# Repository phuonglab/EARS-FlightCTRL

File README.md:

# EARS-ROC
Rocket Onboard Computer designed for amateur rocketry. Light, modular and cheap.

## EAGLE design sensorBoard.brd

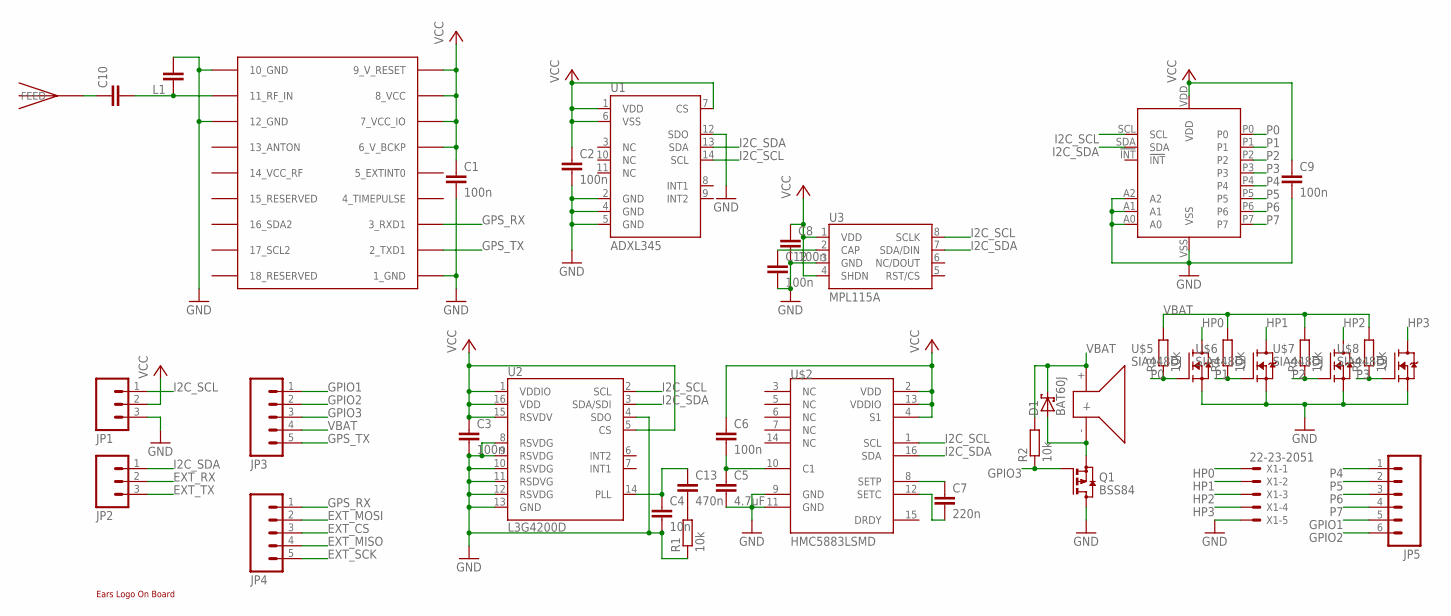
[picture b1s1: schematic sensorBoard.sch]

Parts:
C1, C2, C3, C6, C8, C9, C12: 100n; C0402
C4: 10n; C0402
C5: 4.7uF; C0402
C7: 220n; C0402
C10: C-EUC0603; C0603
C13: 470n; C0402
D1: BAT60J; SOD323_ST
JP1, JP2: M03PTH; 1X03
JP3, JP4: M05PTH; 1X05
JP5: M06SIP; 1X06
L1: C-EUC0603; C0603
Q1: BSS84; SOT23
R1, R2, R3, R4, R5, R6: 10k; R0402
U1: ADXL345; LGA14
U2: L3G4200D; LGA16-4X4
U3: MPL115A; LGA8
U$1: UBLOX_MAX
U$2: HMC5883LSMD; 16LPCC
U$3: KSSG23J12
U$4: PCAL9554B
U$5, U$6, U$7, U$8: SIA448DJ
U$9: JTI_ANTENNA-1575AT43A40
U$10: EARS-LOGO
X1: 22-23-2051

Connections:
EXT_CS: JP4.3
EXT_MISO: JP4.4
EXT_MOSI: JP4.2
EXT_RX: JP2.2
EXT_SCK: JP4.5
EXT_TX: JP2.3
GND: C1.2, C2.2, C3.2, C4.2, C5.2, C8.2, C9.2, C12.2, JP1.3, L1.2, Q1.3 (D), R1.1, U1.2 (GND), U1.4 (GND), U1.5 (GND), U1.12 (SDO), U2.4 (SDO), U2.8 (RSVDG), U2.9 (RSVDG), U2.10 (RSVDG), U2.11 (RSDVG), U2.12 (RSVDG), U2.13 (GND), U3.3 (GND), U$1.1_GND, U$1.10_GND, U$1.12_GND, U$2.9 (GND), U$2.11 (GND), U$4.A0, U$4.A1, U$4.A2, U$4.VSS, U$5.S0 (S), U$5.S4 (S), U$6.S0 (S), U$6.S4 (S), U$7.S0 (S), U$7.S4 (S), U$8.S0 (S), U$8.S4 (S), X1.5
GPIO1: JP3.1, JP5.5
GPIO2: JP3.2, JP5.6
GPIO3: JP3.3, Q1.1 (G), R2.1
GPS_RX: JP4.1, U$1.3_RXD1
GPS_TX: JP3.5, U$1.2_TXD1
HP0: U$5.D0 (D), U$5.D1 (D), U$5.D2 (D), U$5.D5 (D), U$5.D6 (D), X1.1
HP1: U$6.D0 (D), U$6.D1 (D), U$6.D2 (D), U$6.D5 (D), U$6.D6 (D), X1.2
HP2: U$7.D0 (D), U$7.D1 (D), U$7.D2 (D), U$7.D5 (D), U$7.D6 (D), X1.3
HP3: U$8.D0 (D), U$8.D1 (D), U$8.D2 (D), U$8.D5 (D), U$8.D6 (D), X1.4
I2C_SCL: JP1.1, U1.14 (SCL), U2.2 (SCL), U3.8 (SCLK), U$2.1 (SCL), U$4.SCL
I2C_SDA: JP2.1, U1.13 (SDA), U2.3 (SDA/SDI), U3.7 (SDA/DIN), U$2.16 (SDA), U$4.SDA
unnamed: C4.1, C13.1, U2.14 (PLL)
unnamed: C5.1, C6.2, U$2.10 (C1)
unnamed: C7.2, U$2.12 (SETC)
unnamed: C7.1, U$2.8 (SETP)
unnamed: D1.A, Q1.2 (S), U$3.-
unnamed: C10.1, U$9.FEED
unnamed: C10.2, L1.1, U$1.11_RF_IN
unnamed: C12.1, U3.2 (CAP)
unnamed: C13.2, R1.2
P0: R3.1, U$4.P0, U$5.G3 (G)
P1: R4.1, U$4.P1, U$6.G3 (G)
P2: R5.1, U$4.P2, U$7.G3 (G)
P3: R6.1, U$4.P3, U$8.G3 (G)
P4: JP5.1, U$4.P4
P5: JP5.2, U$4.P5
P6: JP5.3, U$4.P6
P7: JP5.4, U$4.P7
VBAT: D1.C, JP3.4, R2.2, R3.2, R4.2, R5.2, R6.2, U$3.+
VCC: C1.1, C2.1, C3.1, C6.1, C8.1, C9.1, JP1.2, U1.1 (VDD), U1.6 (VSS), U1.7 (CS), U2.1 (VDDIO), U2.5 (CS), U2.15 (RSVDV), U2.16 (VDD), U3.1 (VDD), U3.4 (SHDN), U$1.6_V_BCKP, U$1.7_VCC_IO, U$1.8_VCC, U$1.9_V_RESET, U$2.2 (VDD), U$2.4 (S1), U$2.13 (VDDIO), U$4.VDD

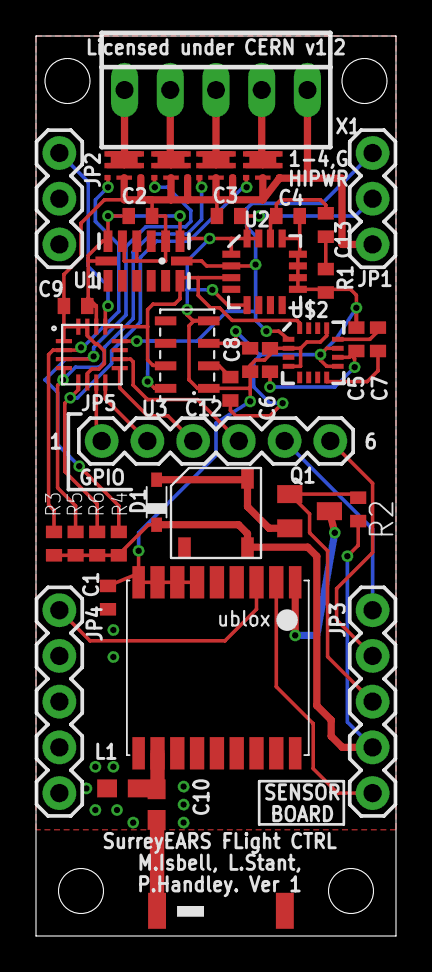
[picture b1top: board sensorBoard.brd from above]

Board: 2 copper layers, 20.0 x 50.0 mm, 40 parts (1 on the bottom side), 31 nets.

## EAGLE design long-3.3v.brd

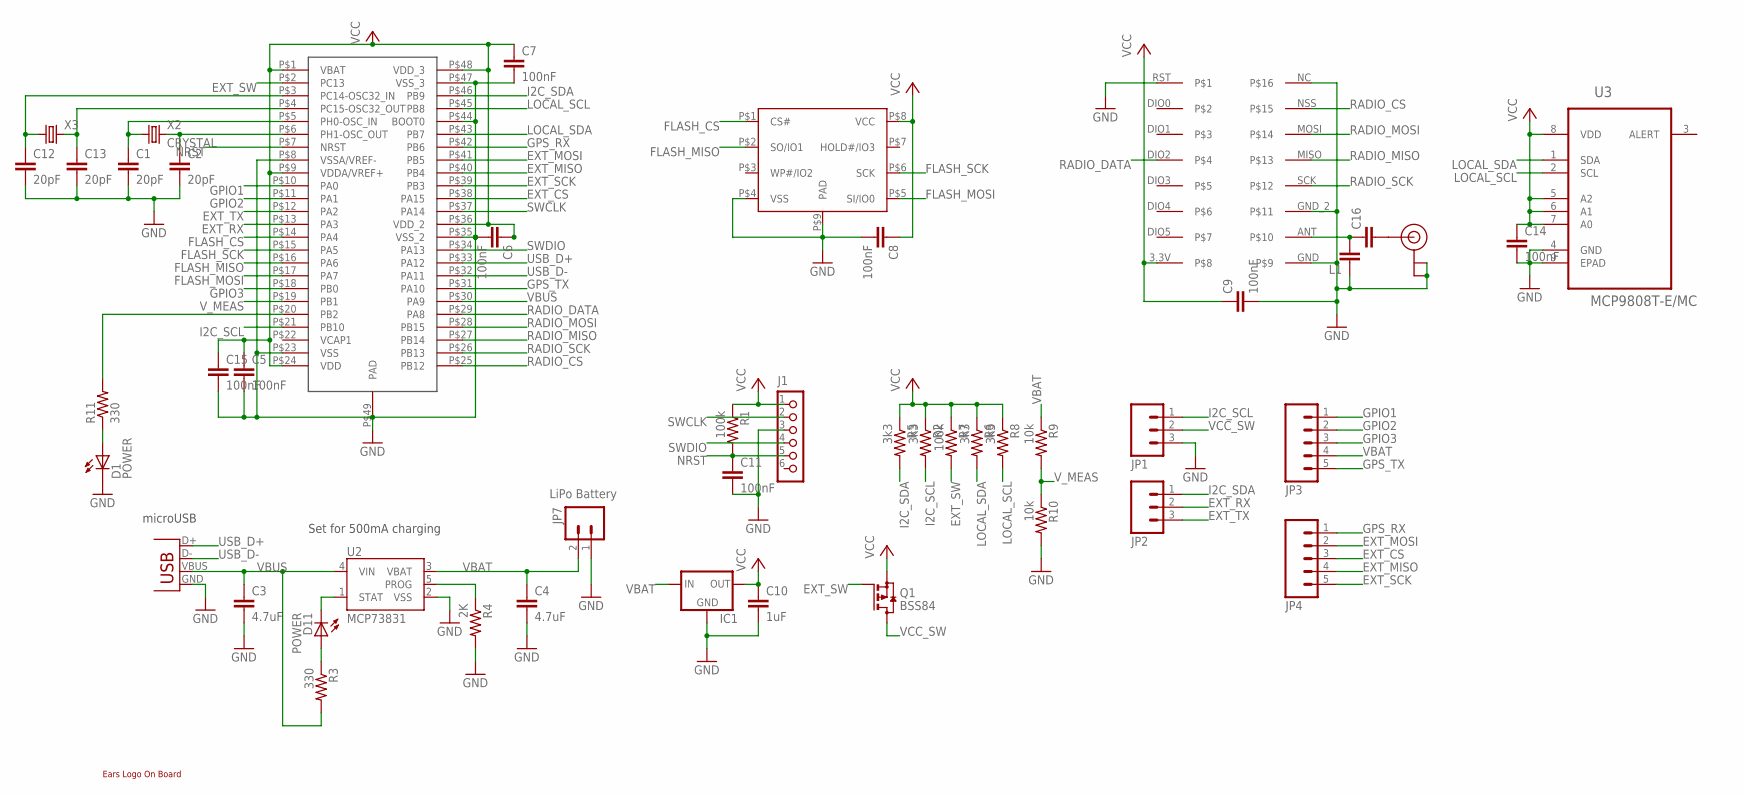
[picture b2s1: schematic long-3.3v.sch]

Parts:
C1, C2, C12, C13: 20pF; C0402
C3, C4: 4.7uF; 0402-CAP
C5, C6, C7, C8, C9, C11, C14, C15: 100nF; C0402
C10: 1uF; C0402
C16: C-EUC0402; C0402
D1, D11: POWER; LED-0603
IC1: XC63FPM; SOT23
J1: CON_HEADER_1X06-SMD-RIGHT-ANGLED; M1X6_MALE_RIGHT_ANGLED_SMD
JP1, JP2: M03PTH; 1X03
JP3, JP4: M05PTH; 1X05
JP7: LiPo Battery; JST-2-SMD
L1: C-EUC0402; C0402
Q1: BSS84; SOT23
R1, R7: 100k; 0402-RES
R2, R5, R6, R8: 3k3; 0402-RES
R3, R11: 330; 0402-RES
R4: 2K; 0402-RES
R9, R10: 10k; 0402-RES
U2: MCP73831; SOT23-5
U3: MCP9808T-E/MC; DFN300X200X100-9N
U$1: STM32F411CEU6
U$2: EARS-LOGO
U$3: RFM69HW
U$4: U.FL
U$5: S25FL256; WSON-8
X1: Micro USB; USB-MICROB
X2: CRYSTAL; ABRACON_ABM3_CRYSTAL
X3: CRYSTALS-NOGND-IQXC-25; 2.0X1.2-2PAD

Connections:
EXT_CS: JP4.3, U$1.P$38 (PA15)
EXT_MISO: JP4.4, U$1.P$40 (PB4)
EXT_MOSI: JP4.2, U$1.P$41 (PB5)
EXT_RX: JP2.2, U$1.P$13 (PA3)
EXT_SCK: JP4.5, U$1.P$39 (PB3)
EXT_SW: Q1.1 (G), R7.2, U$1.P$2 (PC13)
EXT_TX: JP2.3, U$1.P$12 (PA2)
FLASH_CS: U$1.P$14 (PA4), U$5.P$1 (CS#)
FLASH_MISO: U$1.P$16 (PA6), U$5.P$2 (SO/IO1)
FLASH_MOSI: U$1.P$17 (PA7), U$5.P$5 (SI/IO0)
FLASH_SCK: U$1.P$15 (PA5), U$5.P$6 (SCK)
GND: C1.2, C2.2, C3.2, C4.2, C5.2, C6.2, C7.2, C8.2, C9.2, C10.2, C11.2, C12.2, C13.2, C14.2, C15.2, D1.C, IC1.1 (GND), J1.3, JP1.3, JP7.1, L1.1, R4.2, R10.2, U2.2 (VSS), U3.4 (GND), U3.9 (EPAD), U$1.P$8 (VSSA/VREF-), U$1.P$23 (VSS), U$1.P$35 (VSS_2), U$1.P$44 (BOOT0), U$1.P$47 (VSS_3), U$1.P$49 (PAD), U$3.GND, U$3.GND_2, U$3.NC, U$3.RST, U$4.P$1 (GND), U$4.P$2 (GND), U$5.P$4 (VSS), U$5.P$9 (PAD), X1.GND
GPIO1: JP3.1, U$1.P$10 (PA0)
GPIO2: JP3.2, U$1.P$11 (PA1)
GPIO3: JP3.3, U$1.P$18 (PB0)
GPS_RX: JP4.1, U$1.P$42 (PB6)
GPS_TX: JP3.5, U$1.P$31 (PA10)
I2C_SCL: JP1.1, R2.2, U$1.P$21 (PB10)
I2C_SDA: JP2.1, R5.2, U$1.P$46 (PB9)
LOCAL_SCL: R8.2, U3.2 (SCL), U$1.P$45 (PB8)
LOCAL_SDA: R6.2, U3.1 (SDA), U$1.P$43 (PB7)
unnamed: C1.1, U$1.P$5 (PH0-OSC_IN), X2.P$1 (1)
unnamed: C2.1, U$1.P$6 (PH1-OSC_OUT), X2.P$2 (2)
unnamed: D11.A, R3.1
unnamed: C16.2, U$4.P$3 (SIGNAL)
unnamed: C16.1, L1.2, U$3.ANT
unnamed: C13.1, U$1.P$4 (PC15-OSC32_OUT), X3.2
unnamed: C12.1, U$1.P$3 (PC14-OSC32_IN), X3.1
unnamed: D1.A, R11.1
unnamed: R11.2, U$1.P$20 (PB2)
NRST: C11.1, J1.5, R1.2, U$1.P$7 (NRST)
PROG: R4.1, U2.5 (PROG)
RADIO_CS: U$1.P$25 (PB12), U$3.NSS
RADIO_DATA: U$1.P$29 (PA8), U$3.DIO2
RADIO_MISO: U$1.P$27 (PB14), U$3.MISO
RADIO_MOSI: U$1.P$28 (PB15), U$3.MOSI
RADIO_SCK: U$1.P$26 (PB13), U$3.SCK
STAT: D11.C, U2.1 (STAT)
SWCLK: J1.2, U$1.P$37 (PA14)
SWDIO: J1.4, U$1.P$34 (PA13)
USB_D+: U$1.P$33 (PA12), X1.D+
USB_D-: U$1.P$32 (PA11), X1.D-
VBAT: C4.1, IC1.3 (IN), JP3.4, JP7.2, R9.1, U2.3 (VBAT)
VBUS: C3.1, R3.2, U2.4 (VIN), U$1.P$30 (PA9), X1.VBUS
VCC: C5.1, C6.1, C7.1, C8.1, C9.1, C10.1, C14.1, C15.1, IC1.2 (OUT), J1.1, Q1.2 (S), R1.1, R2.1, R5.1, R6.1, R7.1, R8.1, U3.5 (A2), U3.6 (A1), U3.7 (A0), U3.8 (VDD), U$1.P$1 (VBAT), U$1.P$9 (VDDA/VREF+), U$1.P$24 (VDD), U$1.P$36 (VDD_2), U$1.P$48 (VDD_3), U$3.3.3V, U$5.P$8 (VCC)
VCC_SW: JP1.2, Q1.3 (D)
V_MEAS: R9.2, R10.1, U$1.P$19 (PB1)

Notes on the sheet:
Set for 500mA charging
microUSB

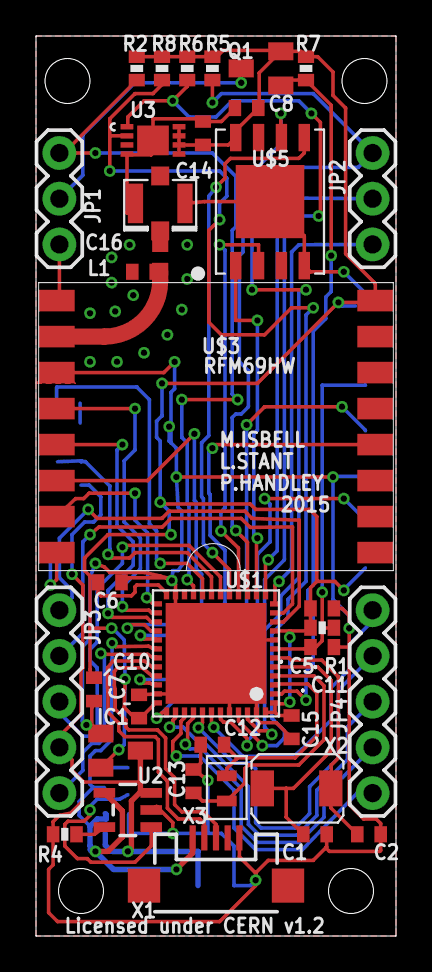
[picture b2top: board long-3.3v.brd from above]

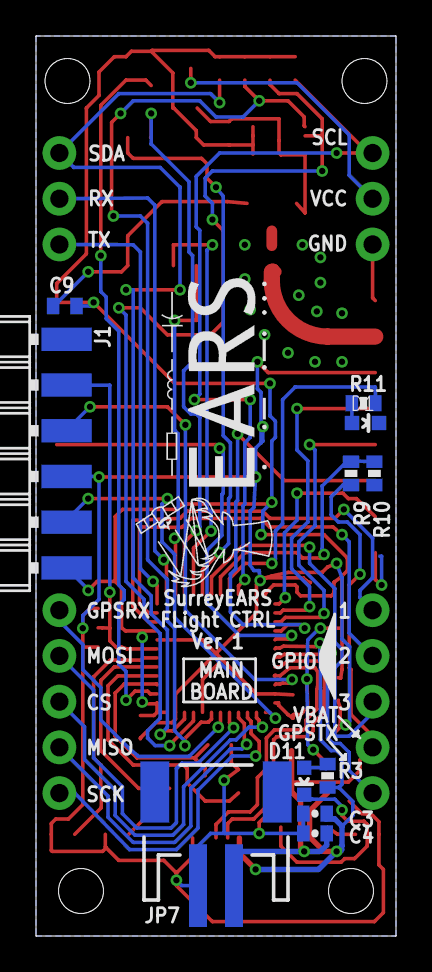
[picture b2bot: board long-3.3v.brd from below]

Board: 2 copper layers, 20.0 x 50.0 mm, 48 parts (12 on the bottom side), 47 nets.

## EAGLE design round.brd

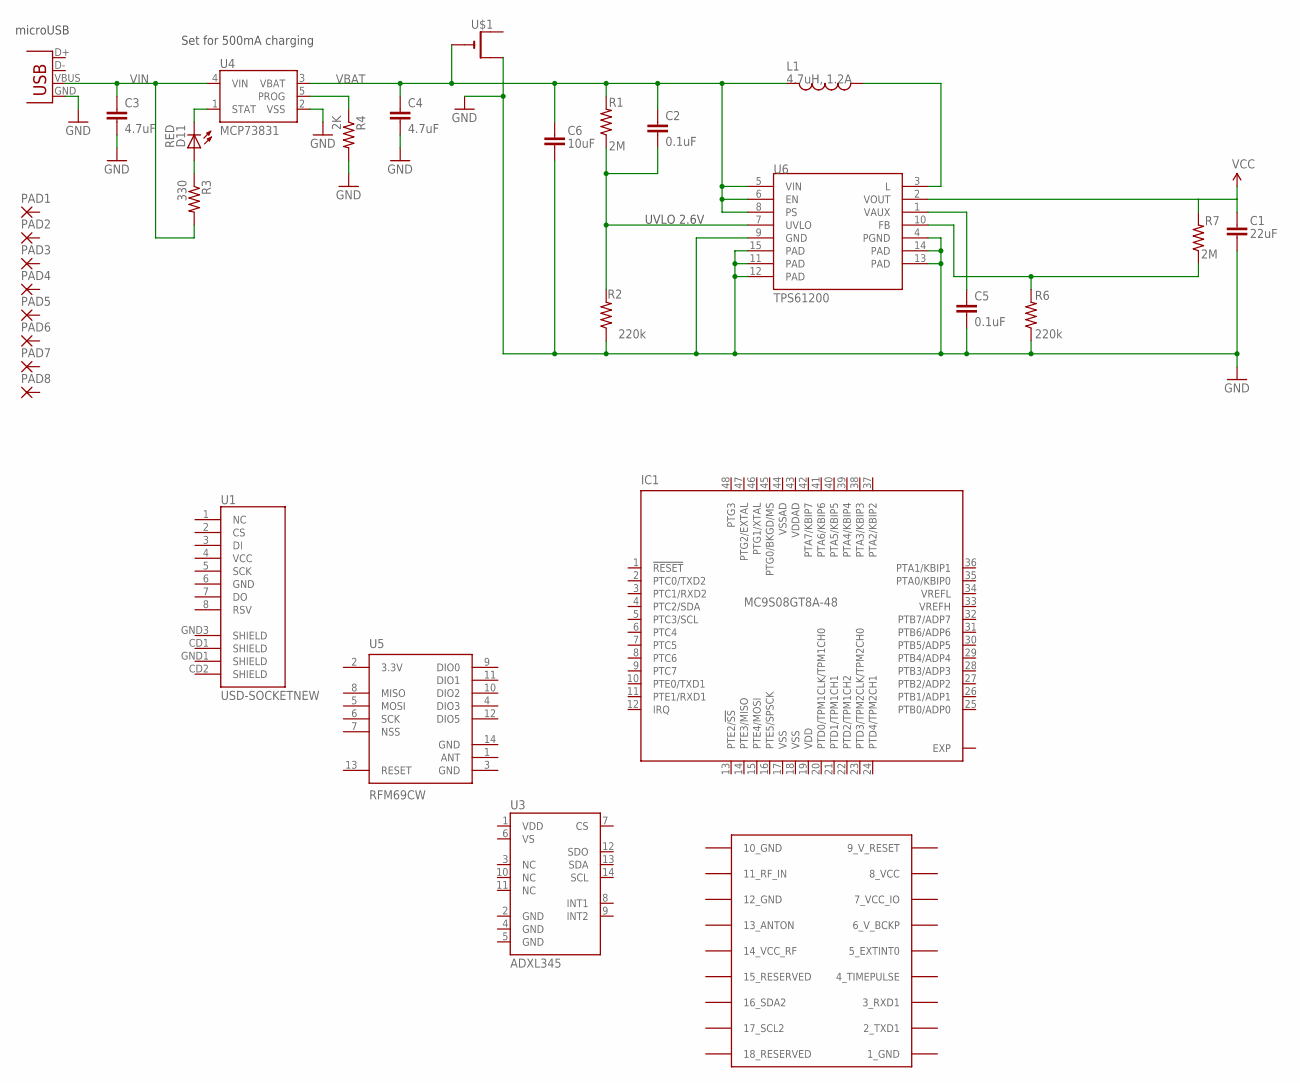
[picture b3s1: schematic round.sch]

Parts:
C1: 22uF; 0805
C2, C5: 0.1uF; 0603-CAP
C3, C4: 4.7uF; 0402-CAP
C6: 10uF; 1206
D11: RED; LED-0603
IC1: MC9S08GT8A-48; QFN48
L1: 4.7uH, 1.2A; CDRH2D09
PAD1, PAD2, PAD3, PAD4, PAD5, PAD6, PAD7, PAD8: 2,15/1,0
R1, R7: 2M; 0603-RES
R2, R6: 220k; 0603-RES
R3: 330; 0402-RES
R4: 2K; 0402-RES
U1: USD-SOCKETNEW; MICRO-SD-SOCKET-PP
U3: ADXL345; LGA14
U4: MCP73831; SOT23-5
U5: RFM69CW; RFM69CW-XXXS2
U6: TPS61200; QFN-10_PAD
U$1: CR1220SMT; CR1220-SMD
U$2: UBLOX_MAX
X1: Micro USB; USB-MICROB

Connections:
1_GND: U$2.1_GND
3.3V: U5.2 (3.3V)
7_VCC_IO: U$2.7_VCC_IO
8_VCC: U$2.8_VCC
9_V_RESET: U$2.9_V_RESET
10_GND: U$2.10_GND
12_GND: U$2.12_GND
FB: R6.2, R7.1, U6.10 (FB)
GND: C1.2, C3.2, C4.2, C5.2, C6.2, R2.1, R4.2, R6.1, U4.2 (VSS), U5.3 (GND), U5.14 (GND), U6.4 (PGND), U6.9 (GND), U6.11 (PAD), U6.12 (PAD), U6.13 (PAD), U6.14 (PAD), U6.15 (PAD), U$1.+$2 (+1), X1.GND
unnamed: C5.1, U6.1 (VAUX)
unnamed: L1.P$1 (1), U6.3 (L)
unnamed: D11.A, R3.1
PROG: R4.1, U4.5 (PROG)
STAT: D11.C, U4.1 (STAT)
UVLO: C2.2, R1.1, R2.2, U6.7 (UVLO)
VBAT: C2.1, C4.1, C6.1, L1.P$2 (2), R1.2, U4.3 (VBAT), U6.5 (VIN), U6.6 (EN), U6.8 (PS), U$1.-
VCC: C1.1, R7.2, U6.2 (VOUT)
VDD: IC1.19 (VDD)
VDDAD: IC1.43 (VDDAD)
VIN: C3.1, R3.2, U4.4 (VIN), X1.VBUS
VSS: IC1.17 (VSS), IC1.18 (VSS)
VSSAD: IC1.44 (VSSAD)

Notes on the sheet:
Set for 500mA charging
microUSB
UVLO 2.6V

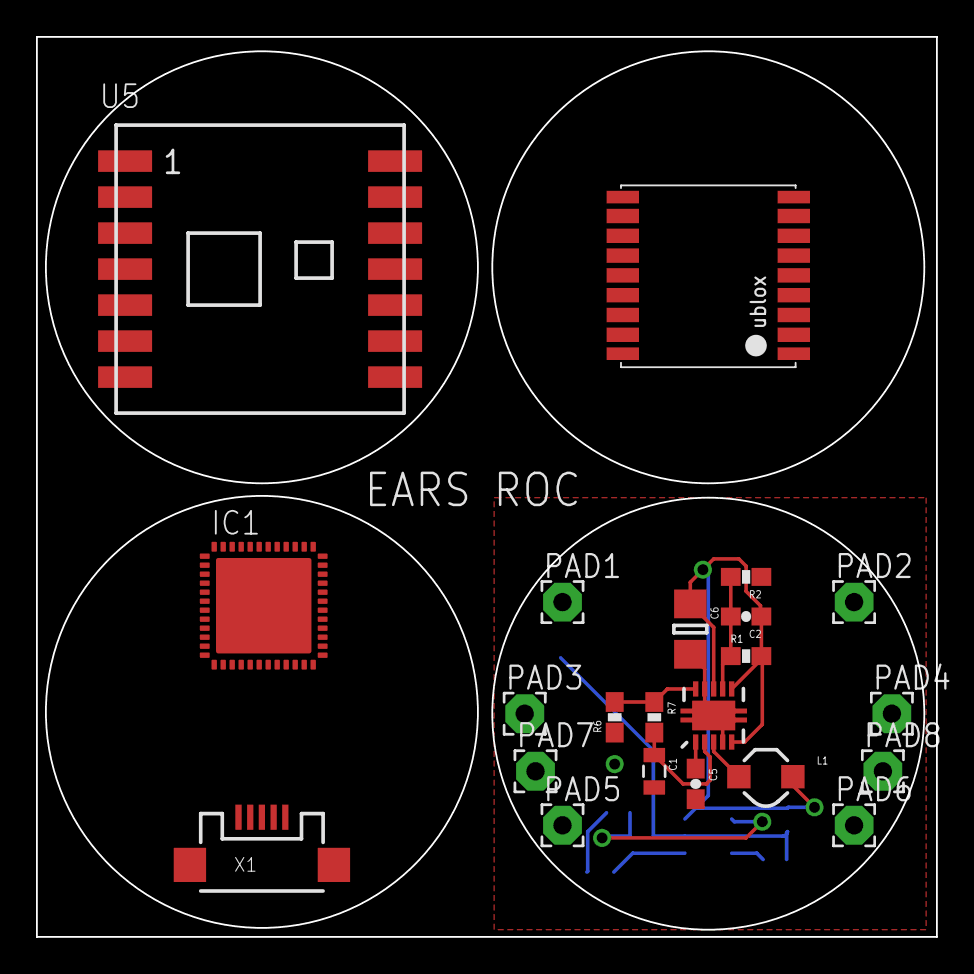
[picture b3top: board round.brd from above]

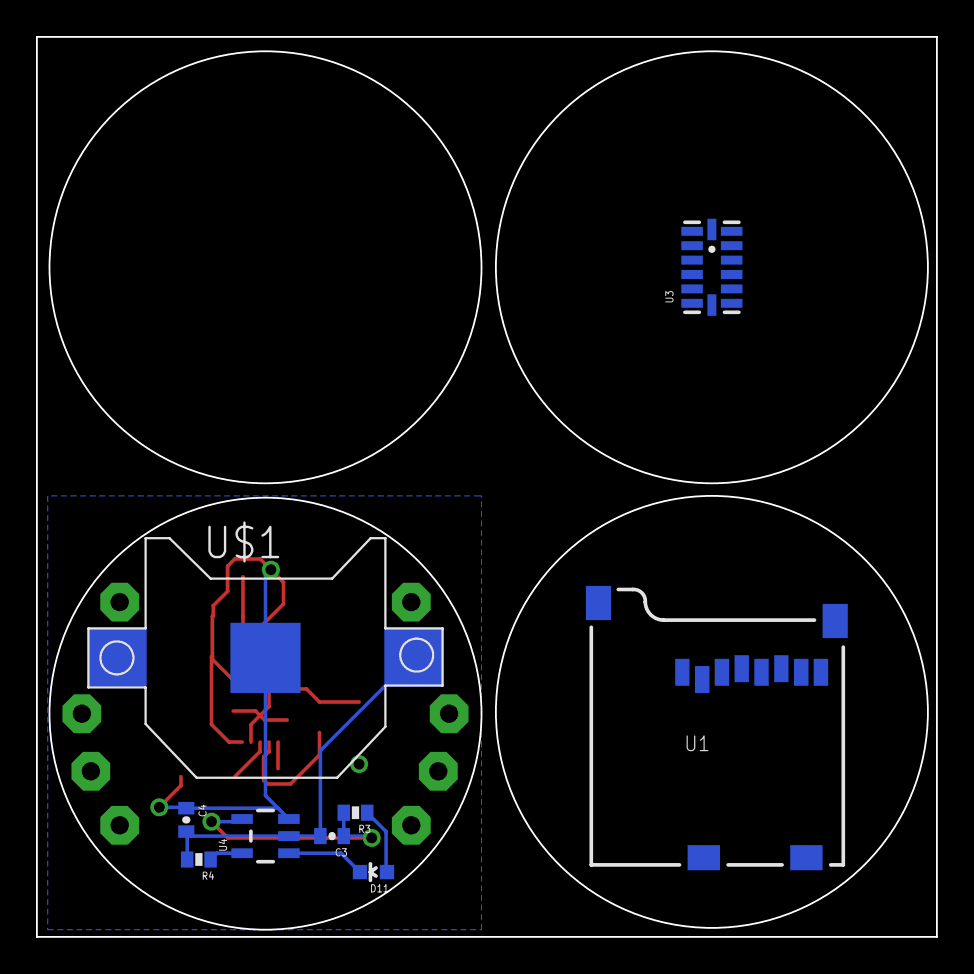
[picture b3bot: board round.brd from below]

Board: 2 copper layers, 50.0 x 50.0 mm, 31 parts (9 on the bottom side), 12 nets.

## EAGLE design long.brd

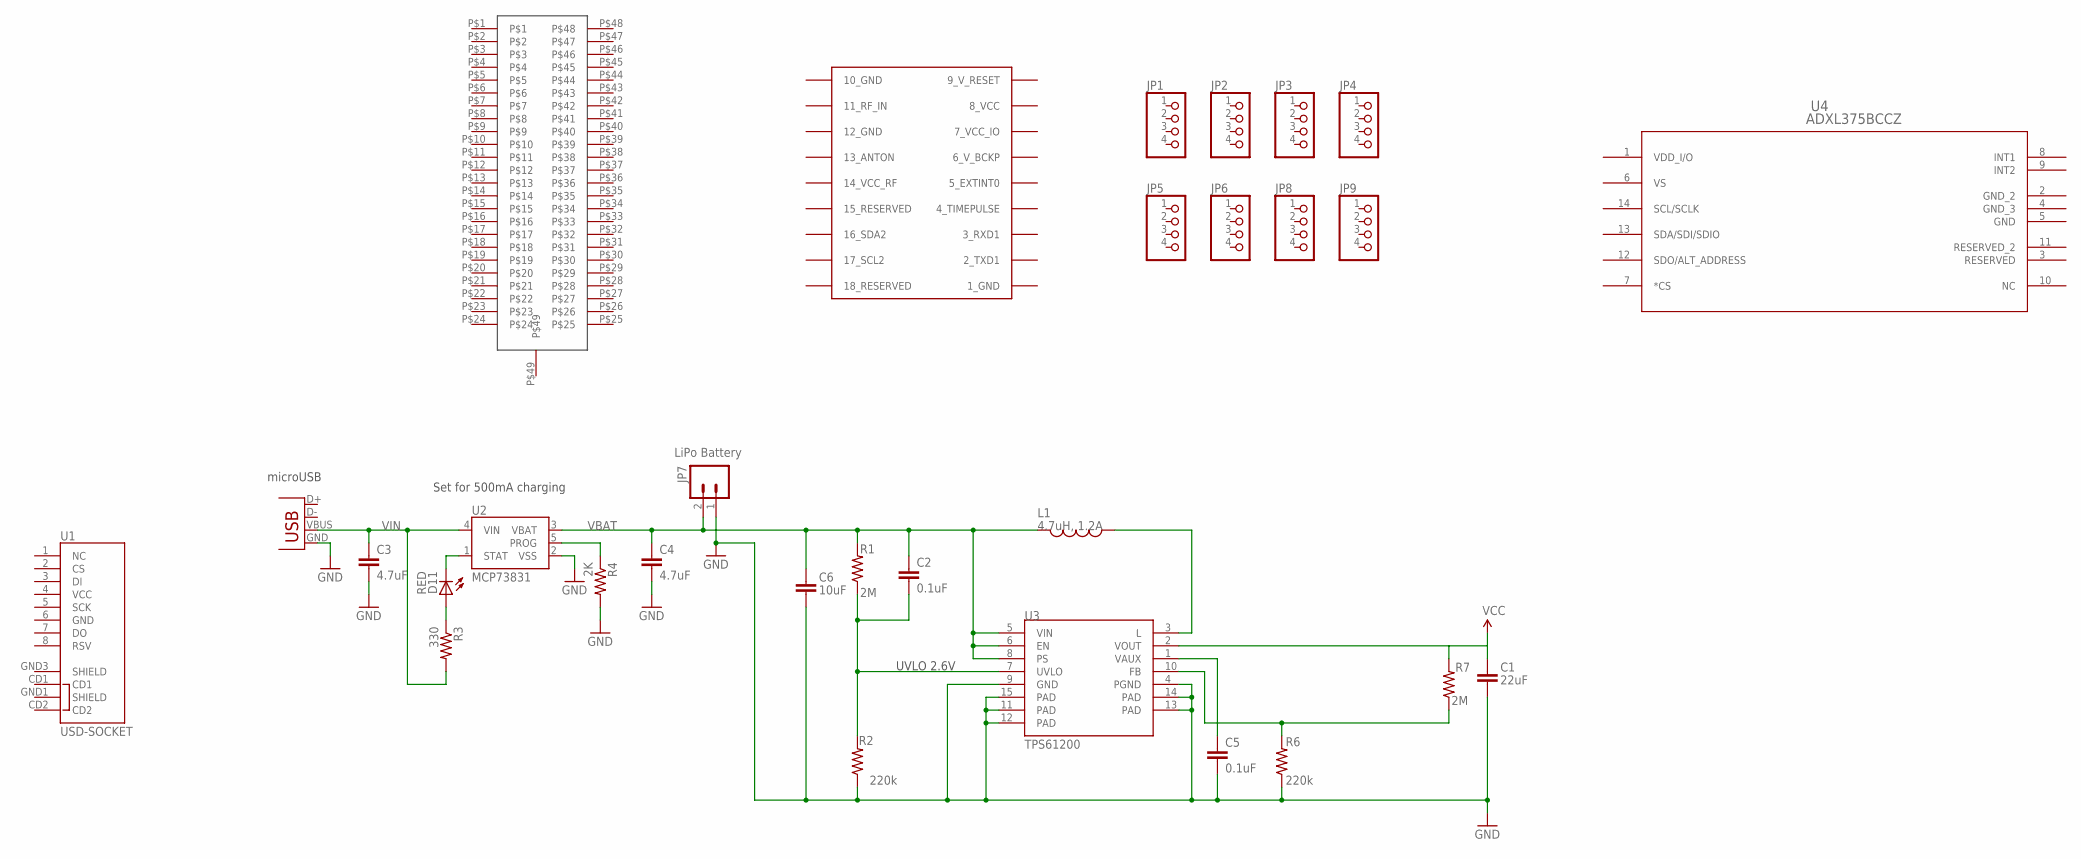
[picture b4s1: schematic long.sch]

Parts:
C1: 22uF; 0805
C2, C5: 0.1uF; 0603-CAP
C3, C4: 4.7uF; 0402-CAP
C6: 10uF; 1206
D11: RED; LED-0603
JP1, JP2, JP3, JP4, JP5, JP6, JP8, JP9: PINHD-1X4; 1X04
JP7: LiPo Battery; JST-2-SMD
L1: 4.7uH, 1.2A; CDRH2D09
R1, R7: 2M; 0603-RES
R2, R6: 220k; 0603-RES
R3: 330; 0402-RES
R4: 2K; 0402-RES
U1: USD-SOCKET; MICROSD_1:1
U2: MCP73831; SOT23-5
U3: TPS61200; QFN-10_PAD
U4: ADXL375BCCZ; LGA_CC-14-1
U$1: STM32F411CEU6
U$2: UBLOX_MAX
X1: Micro USB; USB-MICROB

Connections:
1_GND: U$2.1_GND
7_VCC_IO: U$2.7_VCC_IO
8_VCC: U$2.8_VCC
9_V_RESET: U$2.9_V_RESET
10_GND: U$2.10_GND
12_GND: U$2.12_GND
FB: R6.2, R7.1, U3.10 (FB)
GND: C1.2, C3.2, C4.2, C5.2, C6.2, JP7.1, R2.1, R4.2, R6.1, U2.2 (VSS), U3.4 (PGND), U3.9 (GND), U3.11 (PAD), U3.12 (PAD), U3.13 (PAD), U3.14 (PAD), U3.15 (PAD), X1.GND
unnamed: C5.1, U3.1 (VAUX)
unnamed: L1.P$1 (1), U3.3 (L)
unnamed: D11.A, R3.1
PROG: R4.1, U2.5 (PROG)
STAT: D11.C, U2.1 (STAT)
UVLO: C2.2, R1.1, R2.2, U3.7 (UVLO)
VBAT: C2.1, C4.1, C6.1, JP7.2, L1.P$2 (2), R1.2, U2.3 (VBAT), U3.5 (VIN), U3.6 (EN), U3.8 (PS)
VCC: C1.1, R7.2, U3.2 (VOUT)
VIN: C3.1, R3.2, U2.4 (VIN), X1.VBUS

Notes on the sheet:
Set for 500mA charging
microUSB
UVLO 2.6V

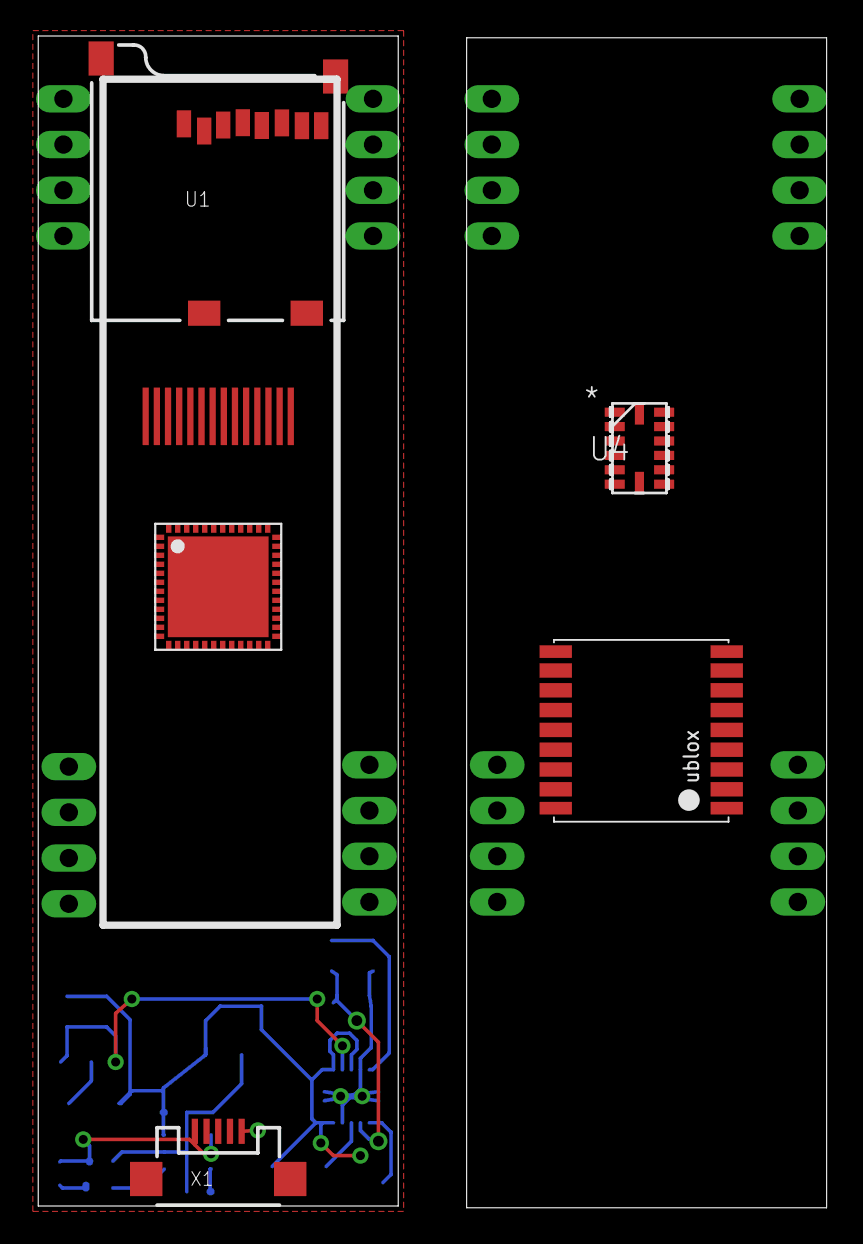
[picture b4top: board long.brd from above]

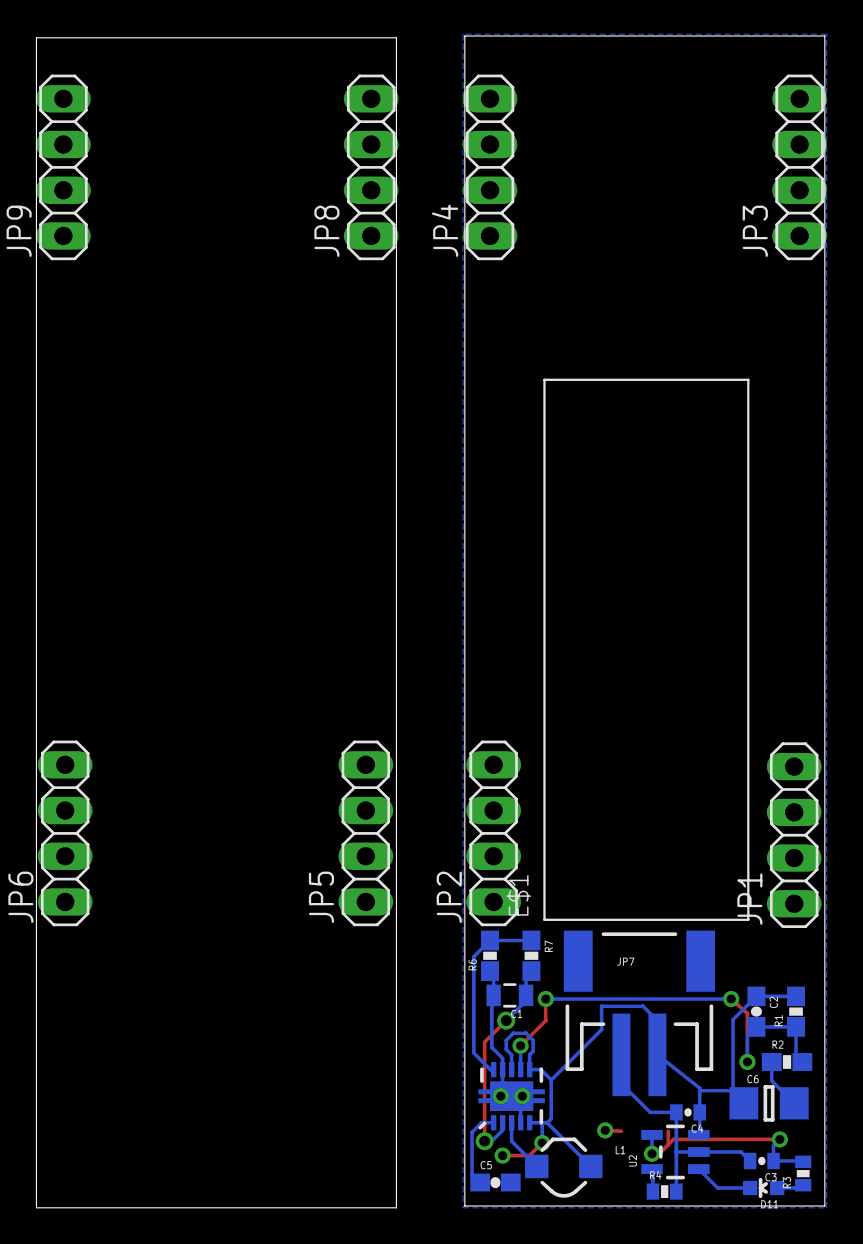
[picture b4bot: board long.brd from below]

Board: 2 copper layers, 43.8 x 65.1 mm, 31 parts (26 on the bottom side), 11 nets.

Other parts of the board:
E$1: UG-2832HSWEG02_WRAPUNDER

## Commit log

2015-05-16 First commit. Will add round boards when I get home!
2015-05-16 tidied up repo
2015-05-16 getting to grips with new Git removals! further tidying
2015-05-16 Completed first draft of power section.
2015-05-16 added artwork
2015-05-17 Added round boards
2015-05-17 Added ADXL375 library
2015-05-18 Added power supply to round boards.
2015-05-21 Added 3.3v only board and made it smaller to fit on 50mm board.
2015-05-26 Added RFM69HW and more stuff
2015-05-31 Updated schematic, connected peripherals
2015-05-31 Connected USB & Crystal Routed base PCB
2015-06-01 Added Components Added decoupling capacitors Changed pin headers to round pads
2015-06-01 Added more parts, routed more lines Added UFL connector (unrouted) Added and routed pullups, programming header, and other stuff
2015-06-02 fixed headers
2015-06-02 fixed pins and added silk text
2015-06-02 connected antenna. NRST needs rerouting.
2015-06-12 Routed antenna in coplanar waveguide. Removed some other tracks to do it though. Matt's turn!
2015-06-26 Updated schematic, unrouted board Added temperature sensor, power switch, 32.768kHz crystal Changed 8MHz crystal Changed connections to micro
2015-06-27 Routed all the things (main board)
2015-07-12 Switched from SD card to Flash memory
2015-07-12 Changed layout, routed board
2015-07-19 New layout routed
2015-07-19 Initial Branch Commit
2015-07-19 done silk and mitred some bends
2015-07-21 Created schematic
2015-07-21 Changed schematic, positioned components
2015-07-21 Board routing complete
2015-07-21 shuffled rf stuffs
2015-07-22 updated RF
2015-07-22 Changed buzzer routed lines
2015-07-22 Peer review complete, freeze design here!
2015-07-22 Stuff checked, freeze design
2015-07-23 Done silk for sensorboard.
2015-07-23 Fixed Silks
2015-07-23 Fixed ground issue
2015-07-23 Added EARS Logo
2015-07-23 Tweaked silkscreen Removed some overlaps Moved Logo
2015-07-23 Added pull-up resistors on mosfets
2015-07-23 Final silk check, added labels and license, shifted rf trace ground plane last time xD
2015-07-23 Changed name on silkscreen
2015-07-23 added template for future mezzanine cards
2015-07-23 started groundstation board
2015-07-26 added logos

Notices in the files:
long-3.3v.brd:
Licensed under CERN v1.2
parts and their libraries:
SparkFun-Connectors: Licensing: Creative Commons ShareAlike 4.0 International - https://creativecommons.org/licenses/by-sa/4.0
